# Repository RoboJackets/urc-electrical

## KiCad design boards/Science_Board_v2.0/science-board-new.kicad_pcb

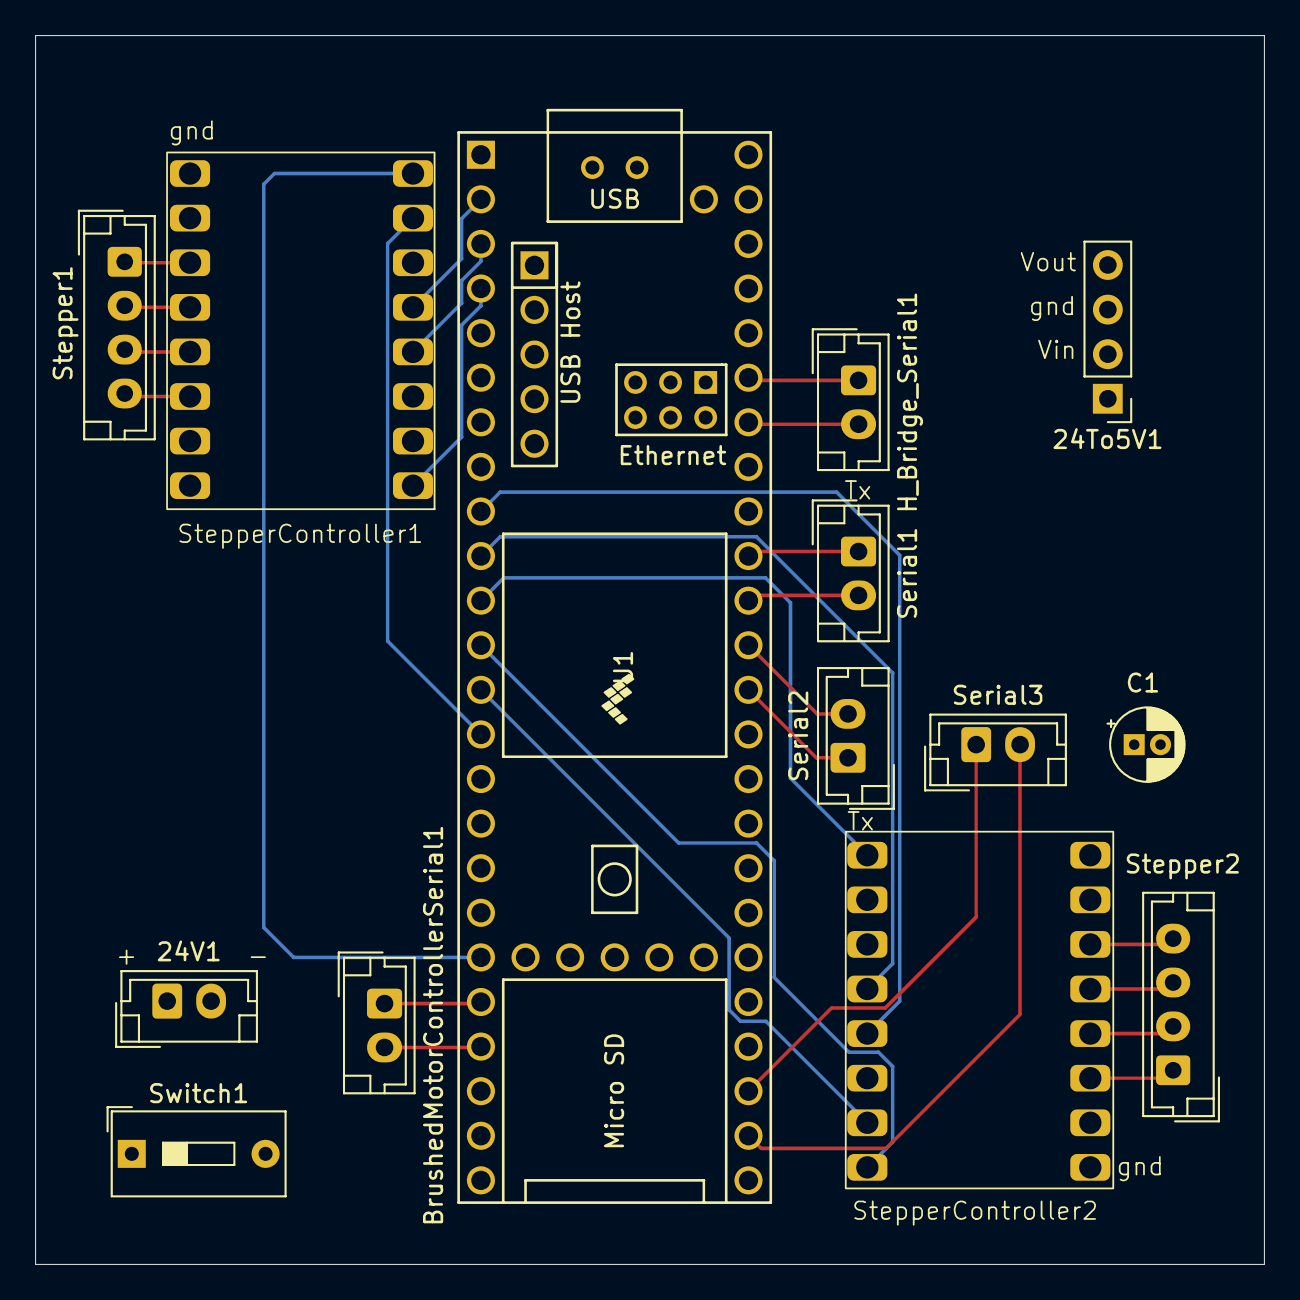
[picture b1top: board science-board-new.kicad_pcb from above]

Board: 4 copper layers, 70.0 x 70.0 mm, 14 parts (0 on the bottom side), 34 nets.

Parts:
24To5V1: PinHeader_1x04_P2.54mm_Vertical
24V1: Conn_01x02; JST_EH_B2B-EH-A_1x02_P2.50mm_Vertical
BrushedMotorControllerSerial1: Conn_01x02; JST_EH_B2B-EH-A_1x02_P2.50mm_Vertical
C1: C; CP_Radial_D4.0mm_P1.50mm
H_Bridge_Serial1: Conn_01x02; JST_EH_B2B-EH-A_1x02_P2.50mm_Vertical
Serial1, Serial2, Serial3: Conn_01x02; JST_EH_B2B-EH-A_1x02_P2.50mm_Vertical
Stepper1, Stepper2: Conn_01x04; JST_EH_B4B-EH-A_1x04_P2.50mm_Vertical
StepperController1, StepperController2: Bigtree_Tech_TMC2209_V1.3
Switch1: SW_DIP_x01; SW_DIP_SPSTx01_Slide_9.78x4.72mm_W7.62mm_P2.54mm
U1: Teensy4.1; Teensy41

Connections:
/3v3_Stepper_Motor_1: StepperController1.15 (VIO), U1.46 (3V3)
/3v3_Stepper_Motor_2: StepperController2.15 (VIO), U1.15 (3V3)
/DIR_Stepper_Motor_1: StepperController1.8 (DIR), U1.19 (27_A13_SCK1)
/DIR_Stepper_Motor_2: StepperController2.8 (DIR), U1.12 (10_CS_MQSR)
/GND_Teensy: 24To5V1.3 (GND), 24V1.2, C1.2, StepperController1.10 (GND), StepperController1.16 (GND), StepperController2.10 (GND), StepperController2.16 (GND), U1.1 (GND), U1.34 (GND), U1.47 (GND)
/OUT_1: StepperController2.1 (EN), U1.11 (9_OUT1C)
/OUT_2: StepperController1.1 (EN), U1.4 (2_OUT2)
/RX_5_H_Bridge: H_Bridge_Serial1.1, U1.43 (21_A7_RX5_BCLK1)
/RX_Serial_1: Serial1.2, U1.38 (16_A2_RX4_SCL1)
/RX_Serial_2: Serial2.2, U1.37 (15_A1_RX3_SPDIF_IN)
/RX_Serial_3: Serial3.2, U1.26 (34_RX8)
/RX_Stepper_Motor_1: StepperController1.5 (TX), U1.2 (0_RX1_CRX2_CS1)
/RX_Stepper_Motor_2: StepperController2.5 (TX), U1.9 (7_RX2_OUT1A)
/RX_drill: BrushedMotorControllerSerial1.1, U1.20 (28_RX7)
/STEP_Stepper_Motor_1: StepperController1.7 (STEP), U1.14 (12_MISO_MQSL)
/STEP_Stepper_Motor_2: StepperController2.7 (STEP), U1.13 (11_MOSI_CTX1)
/TX_5_H_Bridge: H_Bridge_Serial1.2, U1.42 (20_A6_TX5_LRCLK1)
/TX_Serial_1: Serial1.1, U1.39 (17_A3_TX4_SDA1)
/TX_Serial_2: Serial2.1, U1.36 (14_A0_TX3_SPDIF_OUT)
/TX_Serial_3: Serial3.1, U1.27 (35_TX8)
/TX_Stepper_Motor_1: StepperController1.4 (RX), U1.3 (1_TX1_CTX2_MISO1)
/TX_Stepper_Motor_2: StepperController2.4 (RX), U1.10 (8_TX2_IN1)
/TX_drill: BrushedMotorControllerSerial1.2, U1.21 (29_TX7)
unnamed: 24To5V1.2 (Vin), C1.1, StepperController1.9 (VS), StepperController2.9 (VS), Switch1.2
unnamed: 24To5V1.4 (Vout), U1.48 (VIN)
unnamed: 24V1.1, Switch1.1
unnamed: Stepper1.1, StepperController1.14 (B2)
unnamed: Stepper1.2, StepperController1.13 (B1)
unnamed: Stepper1.3, StepperController1.12 (A1)
unnamed: Stepper1.4, StepperController1.11 (A2)
unnamed: Stepper2.1, StepperController2.14 (B2)
unnamed: Stepper2.2, StepperController2.13 (B1)
unnamed: Stepper2.3, StepperController2.12 (A1)
unnamed: Stepper2.4, StepperController2.11 (A2)

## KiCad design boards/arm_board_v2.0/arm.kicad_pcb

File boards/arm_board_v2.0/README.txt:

Imported Library List: 

Teensy symbol and footprints library: 

symbol link:   https://github.com/XenGi/teensy_library

footprints link:   https://github.com/XenGi/teensy.pretty

TMC2209 library: 
symbol and footprints link:   https://www.snapeda.com/parts/TMC2209%20SILENTSTEPSTICK/Trinamic%20Motion%20Control%20GmbH/view-part/

J00-0045NL library: 
symbol and footprints link:   https://www.snapeda.com/parts/J00-0045NL/Pulse%20Electronics%20Network/view-part/

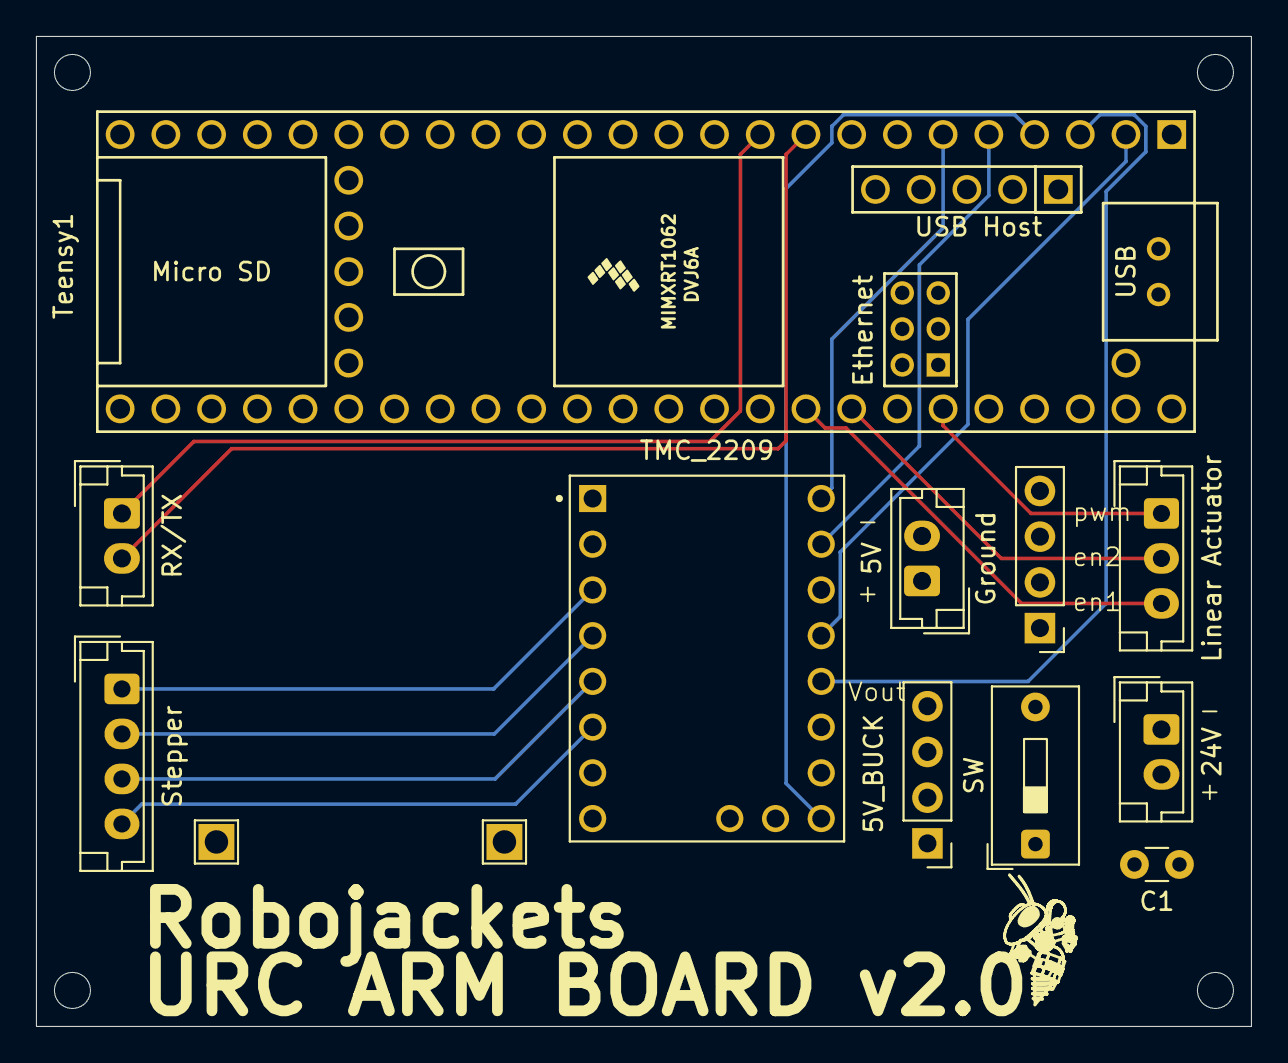
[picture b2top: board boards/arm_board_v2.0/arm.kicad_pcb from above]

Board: 4 copper layers, 67.5 x 55.0 mm, 11 parts (0 on the bottom side), 19 nets.

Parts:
5V: GROUND; JST_EH_B2B-EH-A_1x02_P2.50mm_Vertical
5V_BUCK: PololuD24V5F5; PinHeader_1x04_P2.54mm_Vertical
24V: 24V; JST_EH_B2B-EH-A_1x02_P2.50mm_Vertical
C1: 33 nF; C_Disc_D3.0mm_W1.6mm_P2.50mm
Ground: Output; PinHeader_1x04_P2.54mm_Vertical
Linear Actuator: Actuator; JST_EH_B3B-EH-A_1x03_P2.50mm_Vertical
RX/TX: TX; JST_EH_B2B-EH-A_1x02_P2.50mm_Vertical
SW: SW_DIP_x01; SW_DIP_SPSTx01_Slide_9.78x4.72mm_W7.62mm_P2.54mm
Stepper: Output; JST_EH_B4B-EH-A_1x04_P2.50mm_Vertical
TMC_2209: TMC2209_SILENTSTEPSTICK; MODULE_TMC2209_SILENTSTEPSTICK
Teensy1: Teensy4.1; Teensy41

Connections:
/24V: 5V_BUCK.2 (Vin), C1.1, SW.1, TMC_2209.8 (VM)
/A1: Stepper.1, TMC_2209.3 (MA1)
/A2: Stepper.2, TMC_2209.4 (MA2)
/B1: Stepper.3, TMC_2209.5 (MB1)
/B2: Stepper.4, TMC_2209.6 (MB2)
/Switch: 24V.2, SW.2
/VIO: TMC_2209.2 (VIO), Teensy1.46 (3V3)
/Vin: 5V.1, 5V_BUCK.4 (Vout), Teensy1.48 (VIN)
GND: 5V.2, 5V_BUCK.3 (GND), 24V.1, C1.2, Ground.1, Ground.2, Ground.3, Ground.4, TMC_2209.1 (GND), TMC_2209.7 (GND), Teensy1.47 (GND)
unnamed: Linear Actuator.1, Teensy1.43 (21_A7_RX5_BCLK1)
unnamed: Linear Actuator.2, Teensy1.41 (19_A5_SCL)
unnamed: Linear Actuator.3, Teensy1.40 (18_A4_SDA)
unnamed: RX/TX.1, Teensy1.10 (8_TX2_IN1)
unnamed: RX/TX.2, Teensy1.9 (7_RX2_OUT1A)
unnamed: TMC_2209.9 (DIR), Teensy1.6 (4_BCLK2)
unnamed: TMC_2209.13 (RX), Teensy1.3 (1_TX1_CTX2_MISO1)
unnamed: TMC_2209.10 (STEP), Teensy1.5 (3_LRCLK2)
unnamed: TMC_2209.12 (TX), Teensy1.2 (0_RX1_CRX2_CS1)
unnamed: TMC_2209.16 (~EN), Teensy1.4 (2_OUT2)

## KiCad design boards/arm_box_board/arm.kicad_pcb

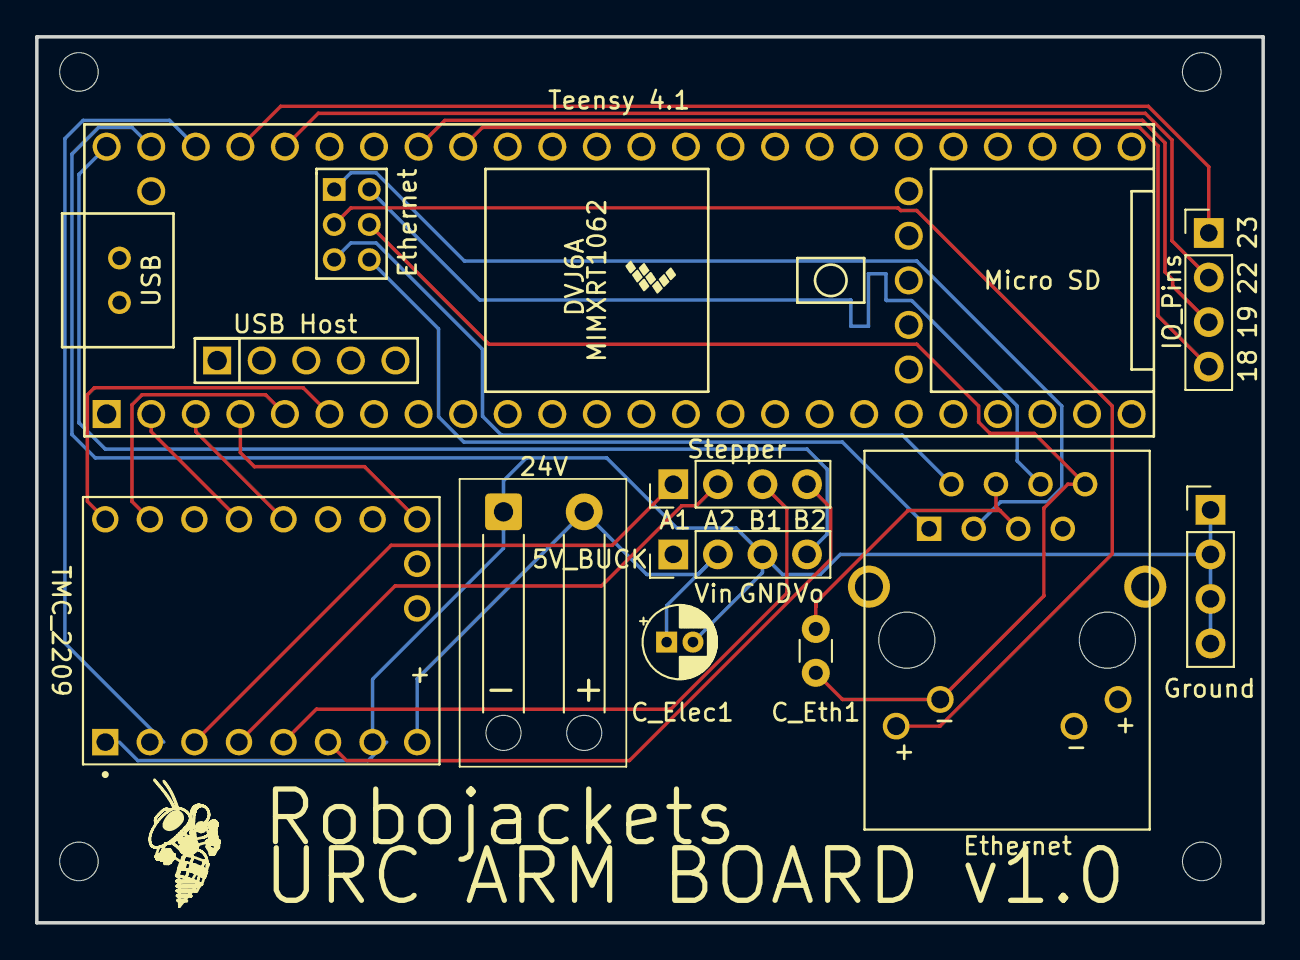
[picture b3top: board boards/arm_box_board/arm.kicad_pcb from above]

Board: 2 copper layers, 69.9 x 50.5 mm, 10 parts (0 on the bottom side), 24 nets.

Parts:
5V_BUCK: PololuD24V5F5; PinHeader_1x04_P2.54mm_Vertical
24V: 24V; SolderWire-0.5sqmm_1x02_P4.6mm_D0.9mm_OD2.1mm_Relief
C_Elec1: C_Large; CP_Radial_D4.0mm_P1.50mm
C_Eth1: C_Small; C_Disc_D3.0mm_W1.6mm_P2.50mm
Ethernet: J00-0045NL; PULSE_J00-0045NL
Ground: Output; PinHeader_1x04_P2.54mm_Vertical
IO_Pins: Output; PinHeader_1x04_P2.54mm_Vertical
Stepper: Output; PinHeader_1x04_P2.54mm_Vertical
TMC_2209: TMC2209_SILENTSTEPSTICK; MODULE_TMC2209_SILENTSTEPSTICK
Teensy 4.1: Teensy4.1; Teensy41

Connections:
/A1: Stepper.1, TMC_2209.3 (MA1)
/A2: Stepper.2, TMC_2209.4 (MA2)
/B1: Stepper.3, TMC_2209.5 (MB1)
/B2: Stepper.4, TMC_2209.6 (MB2)
unnamed: 5V_BUCK.3 (GND), 24V.1, C_Elec1.2, Ground.1, Ground.2, Ground.3, Ground.4, TMC_2209.1 (GND), TMC_2209.7 (GND), Teensy 4.1.47 (GND)
unnamed: 5V_BUCK.2 (Vin), 24V.2, C_Elec1.1, TMC_2209.8 (VM)
unnamed: C_Eth1.1, Ethernet.4 (CTT), Ethernet.5 (CTR)
unnamed: C_Eth1.2, Ethernet.8 (GND), Ethernet.10 (LC), Teensy 4.1.64 (GND)
unnamed: Ethernet.9 (LA), Teensy 4.1.61 (LED)
unnamed: Ethernet.3 (RD+), Teensy 4.1.60 (R+)
unnamed: Ethernet.6 (RD-), Teensy 4.1.65 (R-)
unnamed: Ethernet.1 (TD+), Teensy 4.1.63 (T+)
unnamed: Ethernet.2 (TD-), Teensy 4.1.62 (T-)
unnamed: IO_Pins.1, Teensy 4.1.45 (23_A9_CRX1_MCLK1)
unnamed: IO_Pins.2, Teensy 4.1.44 (22_A8_CTX1)
unnamed: IO_Pins.3, Teensy 4.1.41 (19_A5_SCL)
unnamed: IO_Pins.4, Teensy 4.1.40 (18_A4_SDA)
unnamed: 5V_BUCK.4 (Vout), Teensy 4.1.48 (VIN)
unnamed: TMC_2209.9 (DIR), Teensy 4.1.6 (4_BCLK2)
unnamed: TMC_2209.13 (RX), Teensy 4.1.3 (1_TX1_CTX2_MISO1)
unnamed: TMC_2209.10 (STEP), Teensy 4.1.5 (3_LRCLK2)
unnamed: TMC_2209.12 (TX), Teensy 4.1.2 (0_RX1_CRX2_CS1)
unnamed: TMC_2209.2 (VIO), Teensy 4.1.46 (3V3)
unnamed: TMC_2209.16 (~EN), Teensy 4.1.4 (2_OUT2)

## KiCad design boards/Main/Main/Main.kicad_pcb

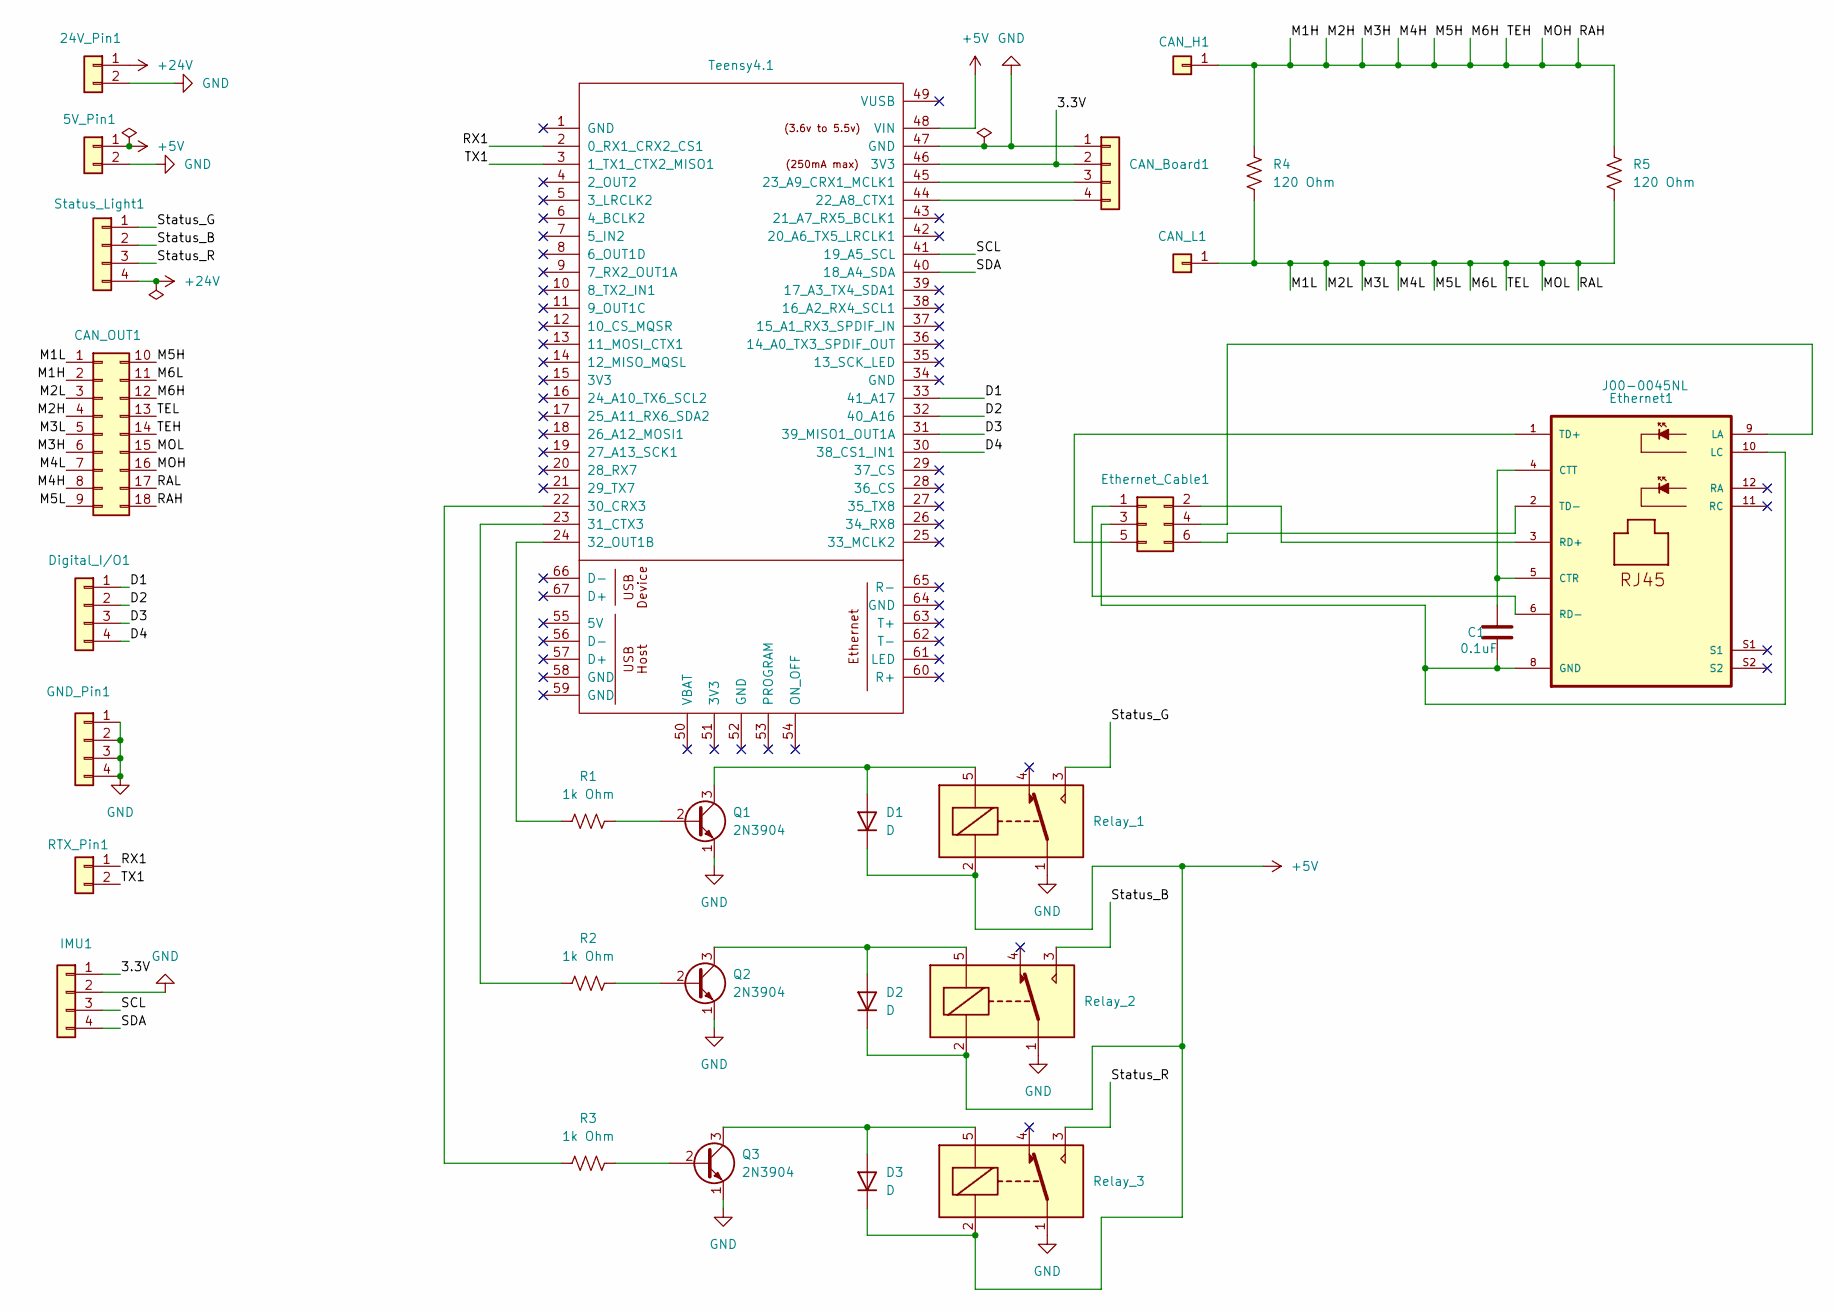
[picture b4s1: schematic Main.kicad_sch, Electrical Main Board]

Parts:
5V_Pin1: 5V; PinHeader_1x02_P2.54mm_Vertical
24V_Pin1: 24V; PinHeader_1x02_P2.54mm_Vertical
C1: 0.1uF; CP_Axial_L10.0mm_D4.5mm_P15.00mm_Horizontal
CAN_Board1: CAN_Board; PinHeader_1x04_P2.54mm_Vertical
CAN_H1: CAN_H; PinHeader_1x01_P2.54mm_Vertical
CAN_L1: CAN_L; PinHeader_1x01_P2.54mm_Vertical
CAN_OUT1: CAN_pins; PinHeader_2x09_P2.54mm_Vertical
D1, D2, D3: D; LED_D5.0mm
Digital_I/O1: Digital I/O; PinHeader_1x04_P2.54mm_Vertical
Ethernet1: J00-0045NL; PULSE_J00-0045NL
Ethernet_Cable1: Conn_02x03_Odd_Even; PinHeader_2x03_P2.54mm_Vertical
GND_Pin1: GND; PinHeader_1x04_P2.54mm_Vertical
IMU1: GND; PinHeader_1x04_P2.54mm_Vertical
Q1, Q2, Q3: 2N3904; TO-92_Inline
R1, R2, R3: 1k Ohm; R_Axial_DIN0309_L9.0mm_D3.2mm_P15.24mm_Horizontal
R4, R5: 120 Ohm; R_Axial_DIN0309_L9.0mm_D3.2mm_P15.24mm_Horizontal
RTX_Pin1: TX/RX; PinHeader_1x02_P2.54mm_Vertical
Relay_1: G5LE1_Green; Relay_SPDT_Omron-G5LE-1
Relay_2: G5LE1_Blue; Relay_SPDT_Omron-G5LE-1
Relay_3: G5LE1_Red; Relay_SPDT_Omron-G5LE-1
Status_Light1: Status_Light; PinHeader_1x04_P2.54mm_Vertical
Teensy4.1: Teensy4.1; Teensy41

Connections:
+5V: 5V_Pin1.1, D1.1 (K), D2.1 (K), D3.1 (K), Relay_1.2, Relay_2.2, Relay_3.2, Teensy4.1.48 (VIN)
+24V: 24V_Pin1.1, Status_Light1.4
/3.3V: CAN_Board1.2, IMU1.1, Teensy4.1.46 (3V3)
/D1: Digital_I/O1.1, Teensy4.1.33 (41_A17)
/D2: Digital_I/O1.2, Teensy4.1.32 (40_A16)
/D3: Digital_I/O1.3, Teensy4.1.31 (39_MISO1_OUT1A)
/D4: Digital_I/O1.4, Teensy4.1.30 (38_CS1_IN1)
/M1H: CAN_H1.1, CAN_OUT1.2, CAN_OUT1.4, CAN_OUT1.6, CAN_OUT1.8, CAN_OUT1.10, CAN_OUT1.12, CAN_OUT1.14, CAN_OUT1.16, CAN_OUT1.18, R4.1, R5.2
/M1L: CAN_L1.1, CAN_OUT1.1, CAN_OUT1.3, CAN_OUT1.5, CAN_OUT1.7, CAN_OUT1.9, CAN_OUT1.11, CAN_OUT1.13, CAN_OUT1.15, CAN_OUT1.17, R4.2, R5.1
/RX1: RTX_Pin1.1, Teensy4.1.2 (0_RX1_CRX2_CS1)
/SCL: IMU1.3, Teensy4.1.41 (19_A5_SCL)
/SDA: IMU1.4, Teensy4.1.40 (18_A4_SDA)
/Status_B: Relay_2.3, Status_Light1.2
/Status_G: Relay_1.3, Status_Light1.1
/Status_R: Relay_3.3, Status_Light1.3
/TX1: RTX_Pin1.2, Teensy4.1.3 (1_TX1_CTX2_MISO1)
GND: 5V_Pin1.2, 24V_Pin1.2, CAN_Board1.1, GND_Pin1.1, GND_Pin1.2, GND_Pin1.3, GND_Pin1.4, IMU1.2, Q1.1 (E), Q2.1 (E), Q3.1 (E), Relay_1.1, Relay_2.1, Relay_3.1, Teensy4.1.47 (GND)
unnamed: CAN_Board1.3, Teensy4.1.45 (23_A9_CRX1_MCLK1)
unnamed: CAN_Board1.4, Teensy4.1.44 (22_A8_CTX1)
unnamed: D1.2 (A), Q1.3 (C), Relay_1.5
unnamed: D2.2 (A), Q2.3 (C), Relay_2.5
unnamed: D3.2 (A), Q3.3 (C), Relay_3.5
unnamed: C1.1, Ethernet1.4 (CTT), Ethernet1.5 (CTR)
unnamed: C1.2, Ethernet1.8 (GND), Ethernet1.10 (LC), Ethernet_Cable1.3
unnamed: Ethernet1.9 (LA), Ethernet_Cable1.4
unnamed: Ethernet1.3 (RD+), Ethernet_Cable1.2
unnamed: Ethernet1.6 (RD-), Ethernet_Cable1.1
unnamed: Ethernet1.1 (TD+), Ethernet_Cable1.5
unnamed: Ethernet1.2 (TD-), Ethernet_Cable1.6
unnamed: Q1.2 (B), R1.2
unnamed: Q2.2 (B), R2.2
unnamed: Q3.2 (B), R3.2
unnamed: R3.1, Teensy4.1.22 (30_CRX3)
unnamed: R2.1, Teensy4.1.23 (31_CTX3)
unnamed: R1.1, Teensy4.1.24 (32_OUT1B)

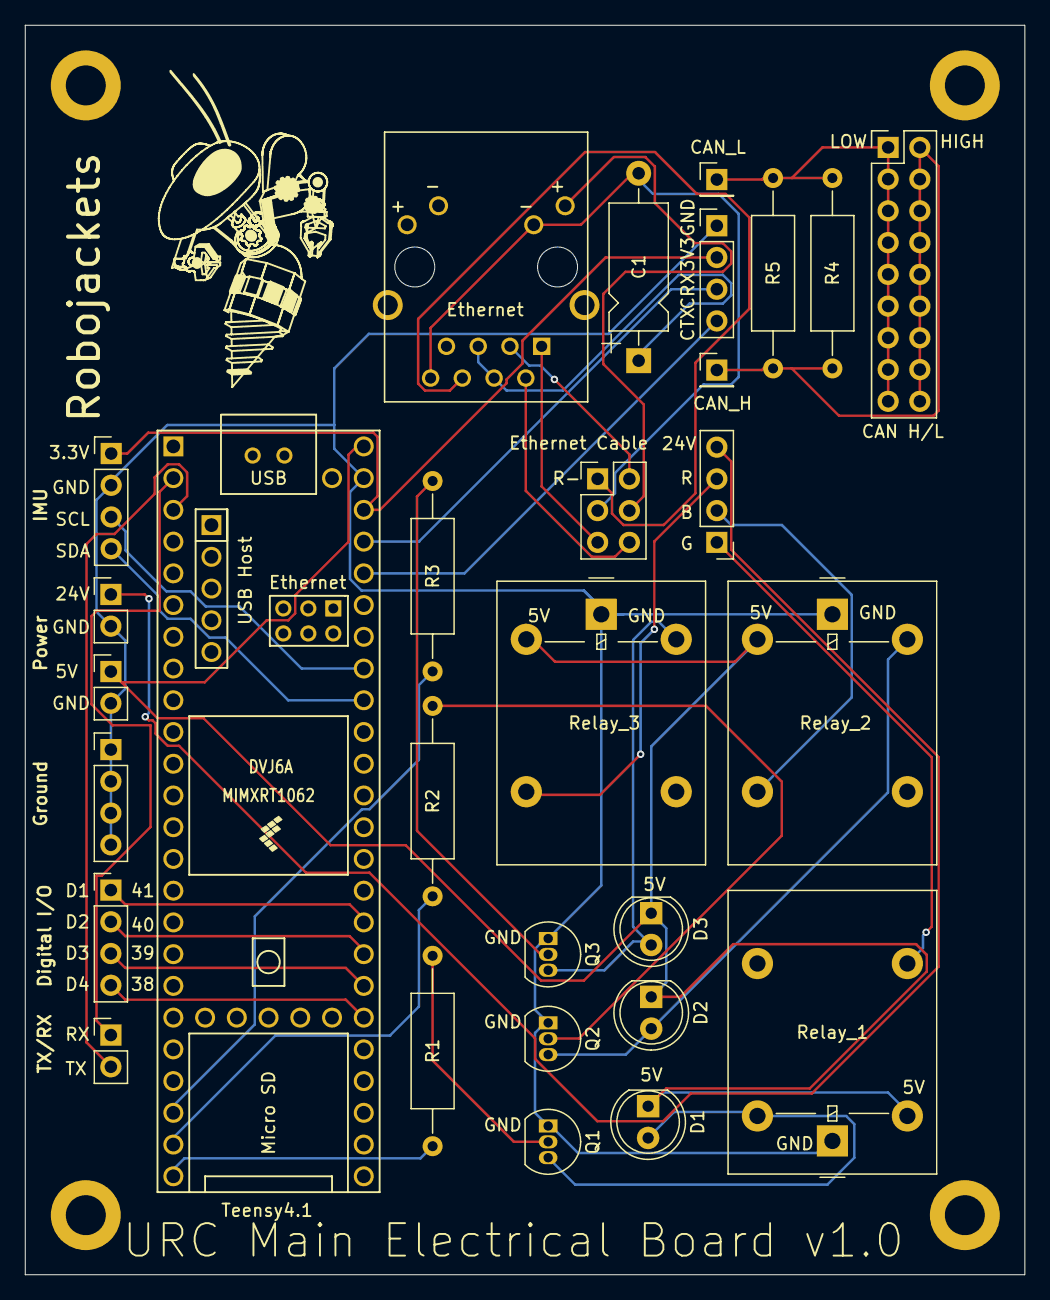
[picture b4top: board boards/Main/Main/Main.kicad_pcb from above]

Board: 2 copper layers, 80.0 x 100.0 mm, 30 parts (0 on the bottom side), 35 nets.

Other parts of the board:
GND: MountingHole_3.2mm_M3_DIN965_Pad

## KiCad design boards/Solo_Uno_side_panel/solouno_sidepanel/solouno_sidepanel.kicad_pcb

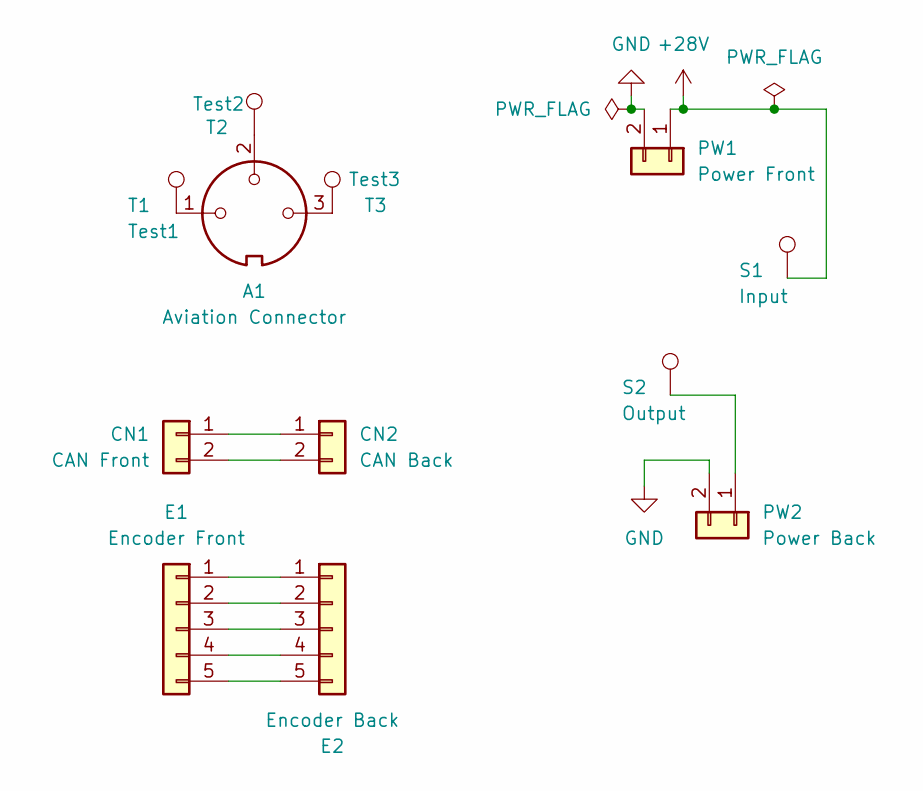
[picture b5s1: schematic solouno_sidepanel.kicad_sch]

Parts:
A1: Aviation Connector; GX-16-3
CN1: CAN Front; JST_EH_B2B-EH-A_1x02_P2.50mm_Vertical
CN2: CAN Back; JST_EH_B2B-EH-A_1x02_P2.50mm_Vertical
E1: Encoder Front; JST_EH_B5B-EH-A_1x05_P2.50mm_Vertical
E2: Encoder Back; JST_EH_B5B-EH-A_1x05_P2.50mm_Vertical
PW1: Power Front; JST_EH_B2B-EH-A_1x02_P2.50mm_Vertical
PW2: Power Back; JST_EH_B2B-EH-A_1x02_P2.50mm_Vertical
S1: Input; TestPoint_Loop_D3.50mm_Drill1.4mm_Beaded
S2: Output; TestPoint_Loop_D3.50mm_Drill1.4mm_Beaded
T1: Test1; TestPoint_Pad_1.5x1.5mm
T2: Test2; TestPoint_Pad_1.5x1.5mm
T3: Test3; TestPoint_Pad_1.5x1.5mm

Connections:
+28V: PW1.1, S1.1
GND: PW1.2, PW2.2
unnamed: A1.1, T1.1
unnamed: A1.2, T2.1
unnamed: A1.3, T3.1
unnamed: CN1.1, CN2.1
unnamed: CN1.2, CN2.2
unnamed: E1.1, E2.1
unnamed: E1.2, E2.2
unnamed: E1.3, E2.3
unnamed: E1.4, E2.4
unnamed: E1.5, E2.5
unnamed: PW2.1, S2.1

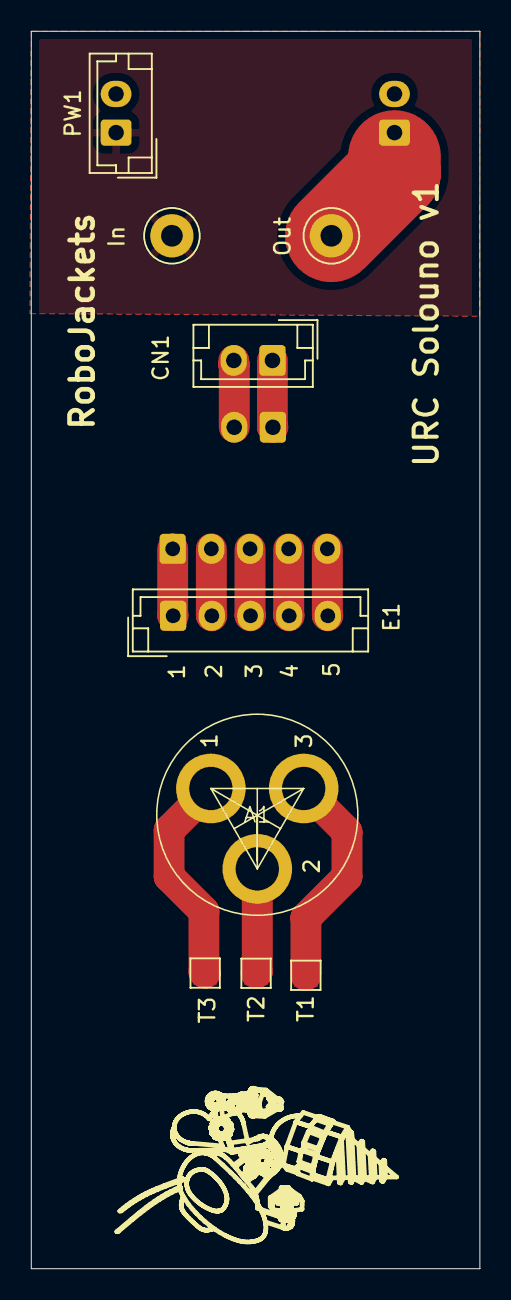
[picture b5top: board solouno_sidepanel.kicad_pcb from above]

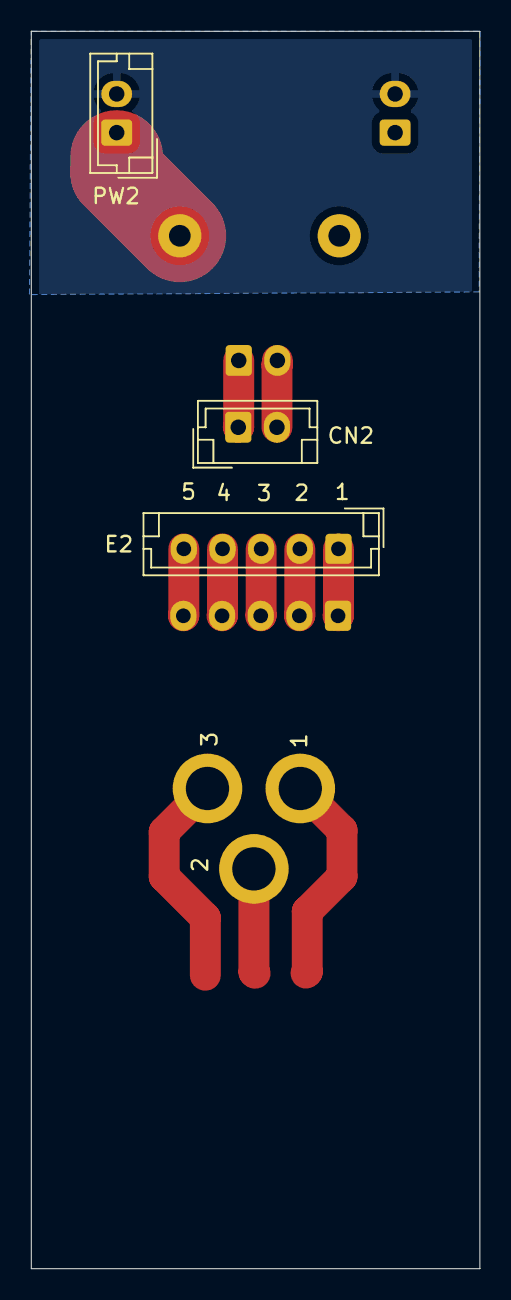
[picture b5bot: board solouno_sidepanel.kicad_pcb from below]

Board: 2 copper layers, 29.0 x 80.0 mm, 12 parts (3 on the bottom side), 13 nets.

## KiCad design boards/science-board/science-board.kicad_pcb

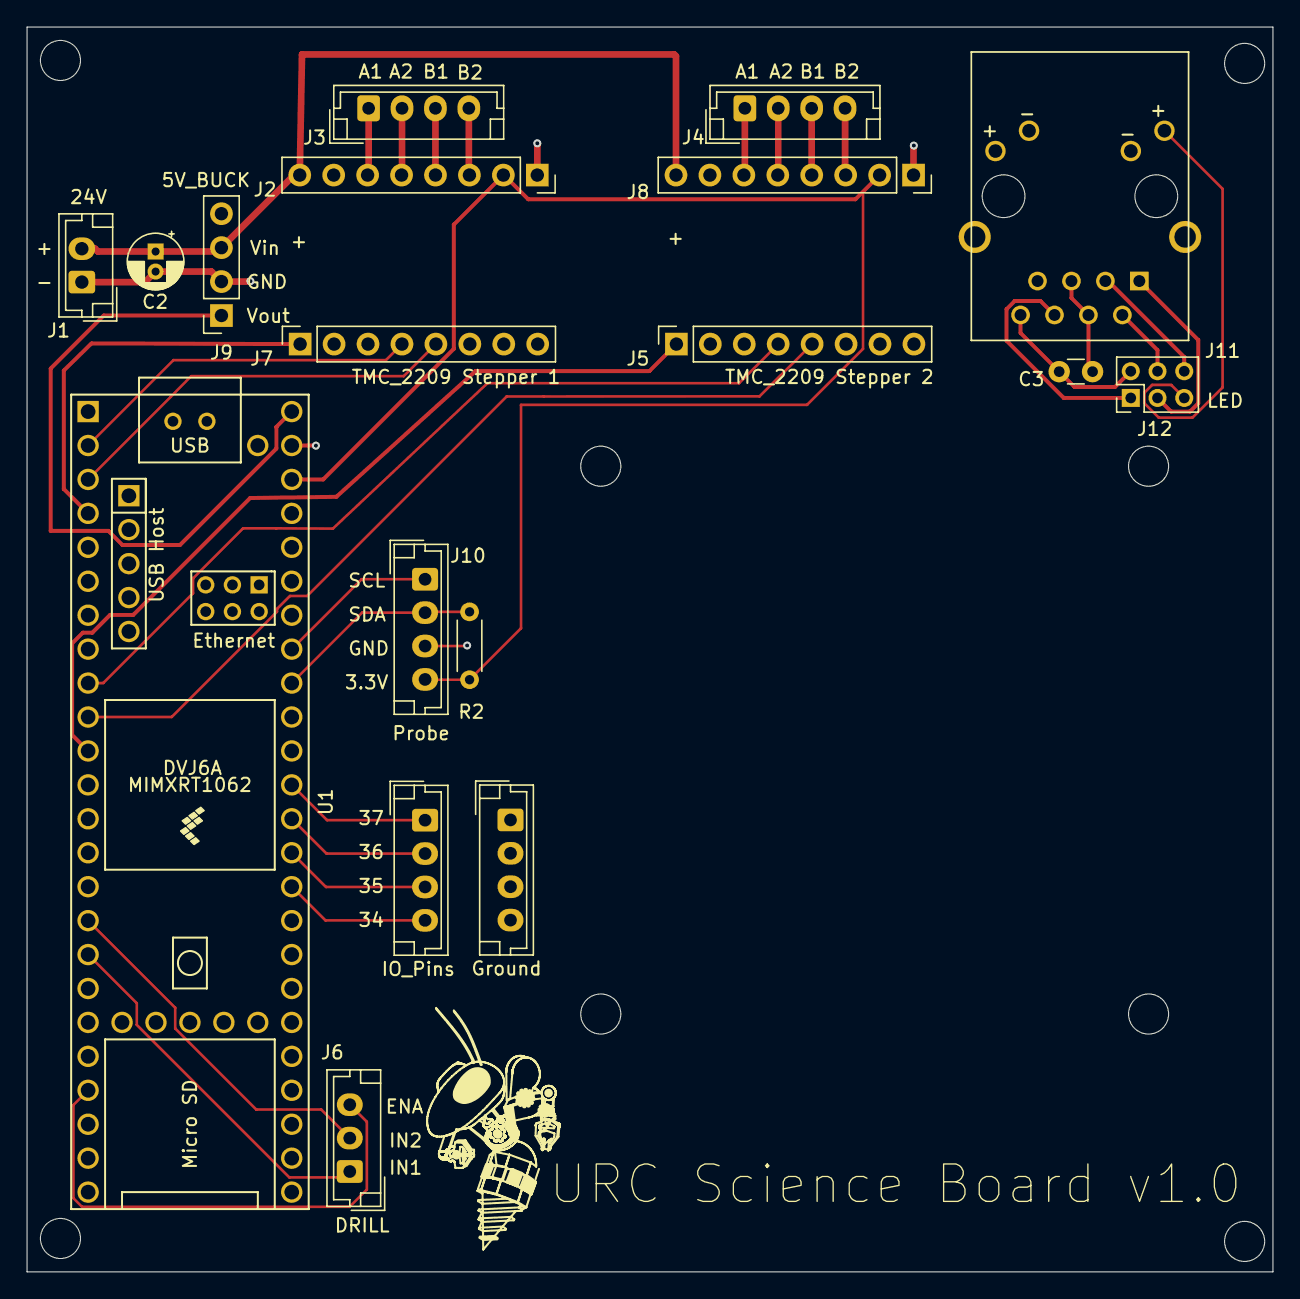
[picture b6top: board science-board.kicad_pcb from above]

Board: 2 copper layers, 93.2 x 93.2 mm, 18 parts (0 on the bottom side), 33 nets.

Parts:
C2: 33uF; CP_Radial_D4.0mm_P1.50mm
C3: 0.1uF; C_Disc_D3.0mm_W1.6mm_P2.50mm
Ground: Conn_01x04; JST_EH_B4B-EH-A_1x04_P2.50mm_Vertical
IO_Pins: Conn_01x04; JST_EH_B4B-EH-A_1x04_P2.50mm_Vertical
J1: Conn_01x02; JST_EH_B2B-EH-A_1x02_P2.50mm_Vertical
J2, J5, J7, J8: Conn_01x08; PinSocket_1x08_P2.54mm_Vertical
J3, J4, J10: Conn_01x04; JST_EH_B4B-EH-A_1x04_P2.50mm_Vertical
J6: Conn_01x03; JST_EH_B3B-EH-A_1x03_P2.50mm_Vertical
J9: Conn_01x04; PinSocket_1x04_P2.54mm_Vertical
J11: J00-0045NL; PULSE_J00-0045NL
J12: Conn_02x03_Counter_Clockwise; PinHeader_2x03_P2.00mm_Vertical
R2: 10k; R_Axial_DIN0204_L3.6mm_D1.6mm_P5.08mm_Horizontal
U1: Teensy4.1; Teensy41

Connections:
+3.3V: J2.2, J8.2, J10.4, R2.2, U1.46 (3V3)
+5V: J9.1, U1.48 (VIN)
+24V: C2.1, J1.2, J2.8, J8.8, J9.3
/34: IO_Pins.4, U1.34 (GND)
/35: IO_Pins.3, U1.35 (13_SCK_LED)
/36: IO_Pins.2, U1.36 (14_A0_TX3_SPDIF_OUT)
/37: IO_Pins.1, U1.37 (15_A1_RX3_SPDIF_IN)
/CTR: C3.1, J11.4 (CTT), J11.5 (CTR)
/D1_A1: J2.5, J3.2
/D1_A2: J2.6, J3.1
/D1_B1: J2.4, J3.3
/D1_B2: J2.3, J3.4
/D1_EN: J7.1, U1.4 (2_OUT2)
/D1_RX: J7.5, U1.3 (1_TX1_CTX2_MISO1)
/D1_TX: J7.4, U1.2 (0_RX1_CRX2_CS1)
/D2_A1: J4.2, J8.5
/D2_A2: J4.1, J8.6
/D2_B1: J4.3, J8.4
/D2_B2: J4.4, J8.3
/D2_EN: J5.1, U1.11 (9_OUT1C)
/D2_RX: J5.5, U1.10 (8_TX2_IN1)
/D2_TX: J5.4, U1.9 (7_RX2_OUT1A)
/EN1: J6.1, U1.17 (25_A11_RX6_SDA2)
/EN2: J6.2, U1.16 (24_A10_TX6_SCL2)
/ENA: J6.3, U1.21 (29_TX7)
/LED: J11.9 (LA), J12.5
/RX+: J11.3 (RD+), J12.6
/RX-: J11.6 (RD-), J12.1
/TX+: J11.1 (TD+), J12.3
/TX-: J11.2 (TD-), J12.4
GND: C2.2, C3.2, Ground.1, Ground.2, Ground.3, Ground.4, J1.1, J2.1, J2.7, J8.1, J8.7, J9.2, J10.3, J11.8 (GND), J11.10 (LC), J12.2, U1.47 (GND)
SCL: J10.1, U1.41 (19_A5_SCL)
SDA: J10.2, R2.1, U1.40 (18_A4_SDA)

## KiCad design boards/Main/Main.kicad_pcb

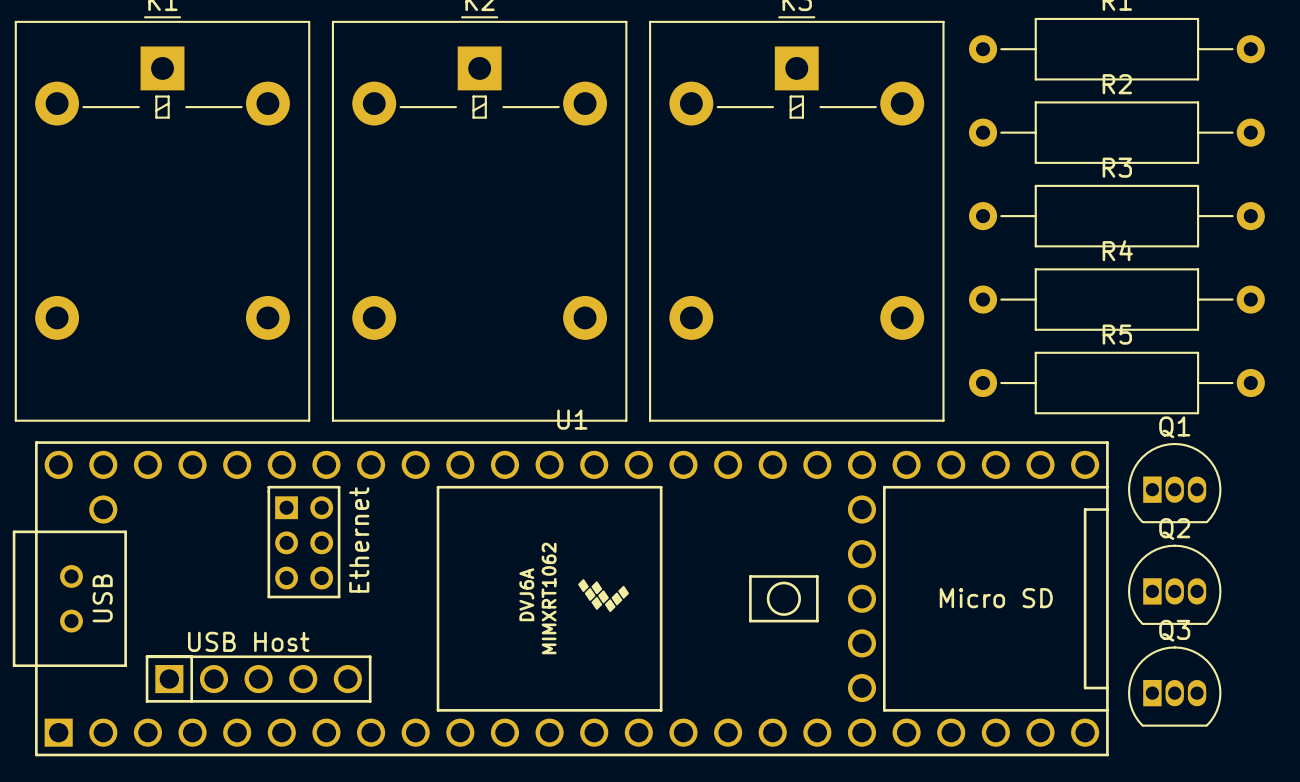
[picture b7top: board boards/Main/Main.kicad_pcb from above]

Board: 2 copper layers, 12 parts (0 on the bottom side), 12 nets, no tracks yet.

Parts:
K1, K2, K3: G5LE-1; Relay_SPDT_Omron-G5LE-1
Q1, Q2, Q3: 2N3904; TO-92_Inline
R1, R2, R3, R4, R5: 100 Ohm; R_Axial_DIN0309_L9.0mm_D3.2mm_P15.24mm_Horizontal
U1: Teensy4.1; Teensy41

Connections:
+5V: K1.2, K2.2, K3.2, U1.48 (VIN)
/M1L: R4.2, R5.1
GND: K1.1, K2.1, K3.1, Q1.1 (E), Q2.1 (E), Q3.1 (E), U1.1 (GND), U1.47 (GND)
unnamed: K1.5, Q2.3 (C)
unnamed: K2.5, Q1.3 (C)
unnamed: K3.5, Q3.3 (C)
unnamed: Q1.2 (B), R2.2
unnamed: Q2.2 (B), R1.2
unnamed: Q3.2 (B), R3.2
unnamed: R3.1, U1.22 (30_CRX3)
unnamed: R2.1, U1.23 (31_CTX3)
unnamed: R1.1, U1.24 (32_OUT1B)

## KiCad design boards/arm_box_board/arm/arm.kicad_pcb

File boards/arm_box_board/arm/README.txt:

Imported Library List: 

Teensy symbol and footprints library: 

symbol link:   https://github.com/XenGi/teensy_library
footprints link:   https://github.com/XenGi/teensy.pretty

TMC2209 library: 

symbol and footprints link:   https://www.snapeda.com/parts/TMC2209%20SILENTSTEPSTICK/Trinamic%20Motion%20Control%20GmbH/view-part/

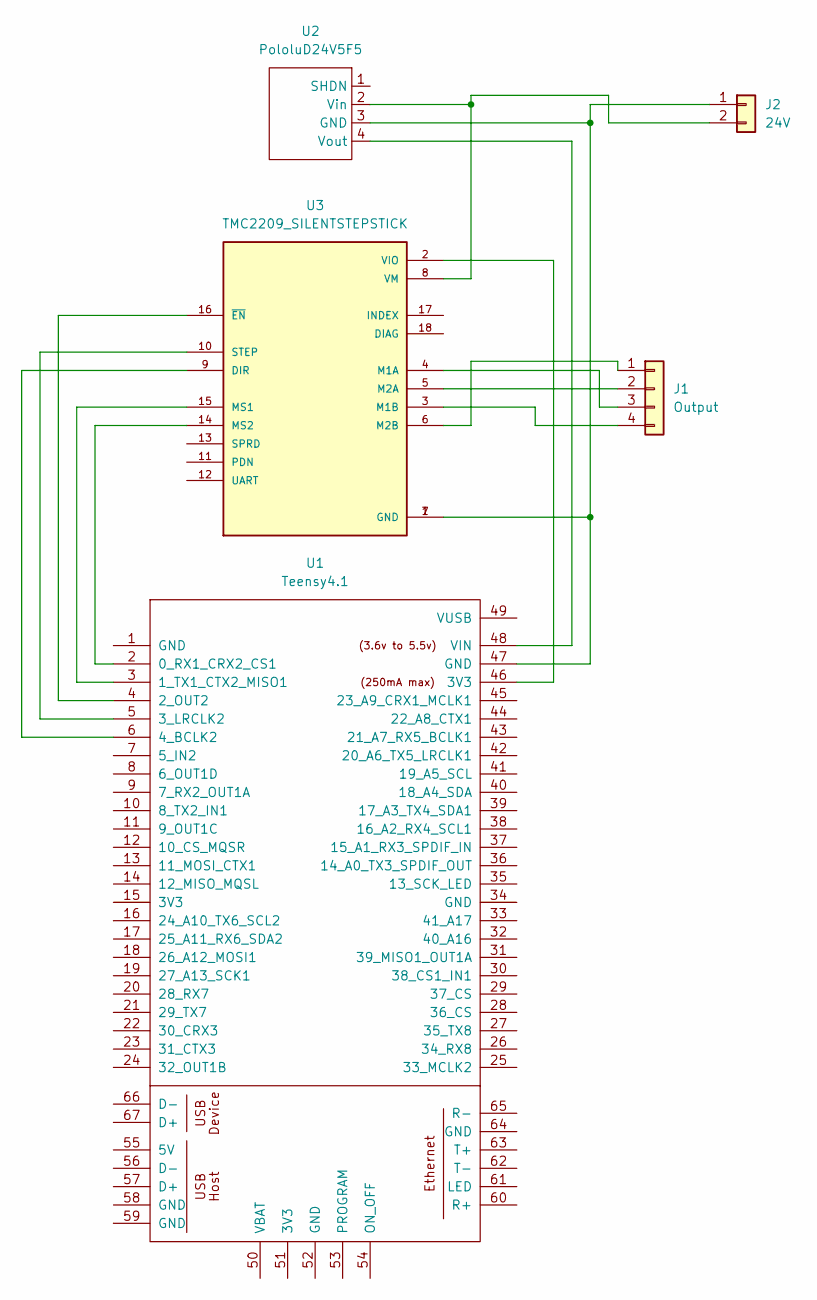
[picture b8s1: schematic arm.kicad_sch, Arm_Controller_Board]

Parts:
J1: Output; PinHeader_1x04_P2.54mm_Vertical
J2: 24V; SolderWire-0.5sqmm_1x02_P4.6mm_D0.9mm_OD2.1mm_Relief
U1: Teensy4.1; Teensy41
U2: PololuD24V5F5; PinHeader_1x04_P2.54mm_Vertical
U3: TMC2209_SILENTSTEPSTICK; MODULE_TMC2209_SILENTSTEPSTICK; PARTREV 1.20

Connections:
unnamed: J1.1, U3.6 (M2B)
unnamed: J1.2, U3.5 (M2A)
unnamed: J1.3, U3.4 (M1A)
unnamed: J1.4, U3.3 (M1B)
unnamed: J2.1, U1.47 (GND), U2.3 (GND), U3.1 (GND), U3.7 (GND)
unnamed: J2.2, U2.2 (Vin), U3.8 (VM)
unnamed: U1.2 (0_RX1_CRX2_CS1), U3.14 (MS2)
unnamed: U1.3 (1_TX1_CTX2_MISO1), U3.15 (MS1)
unnamed: U1.4 (2_OUT2), U3.16 (~EN)
unnamed: U1.5 (3_LRCLK2), U3.10 (STEP)
unnamed: U1.6 (4_BCLK2), U3.9 (DIR)
unnamed: U1.48 (VIN), U2.4 (Vout)
unnamed: U1.46 (3V3), U3.2 (VIO)
